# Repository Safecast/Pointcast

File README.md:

# Pointcast V1.0
New generation nGeigie (work in progress)

Uploads are done through the gateway and go to http://dev.safecast.org

simple software setup:
  - arduino ide 
  - teensyduino or teensy application for uploading hex file into Teensy
  - upgrade firmware instructions are at https://docs.google.com/document/d/16hdhQj_UQkusotejkor8-5BlaK_a2mFPmyVPtsAJ4F8/edit?usp=sharing

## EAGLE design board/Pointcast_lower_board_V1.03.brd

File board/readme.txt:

Files are cretaed in Eagle software

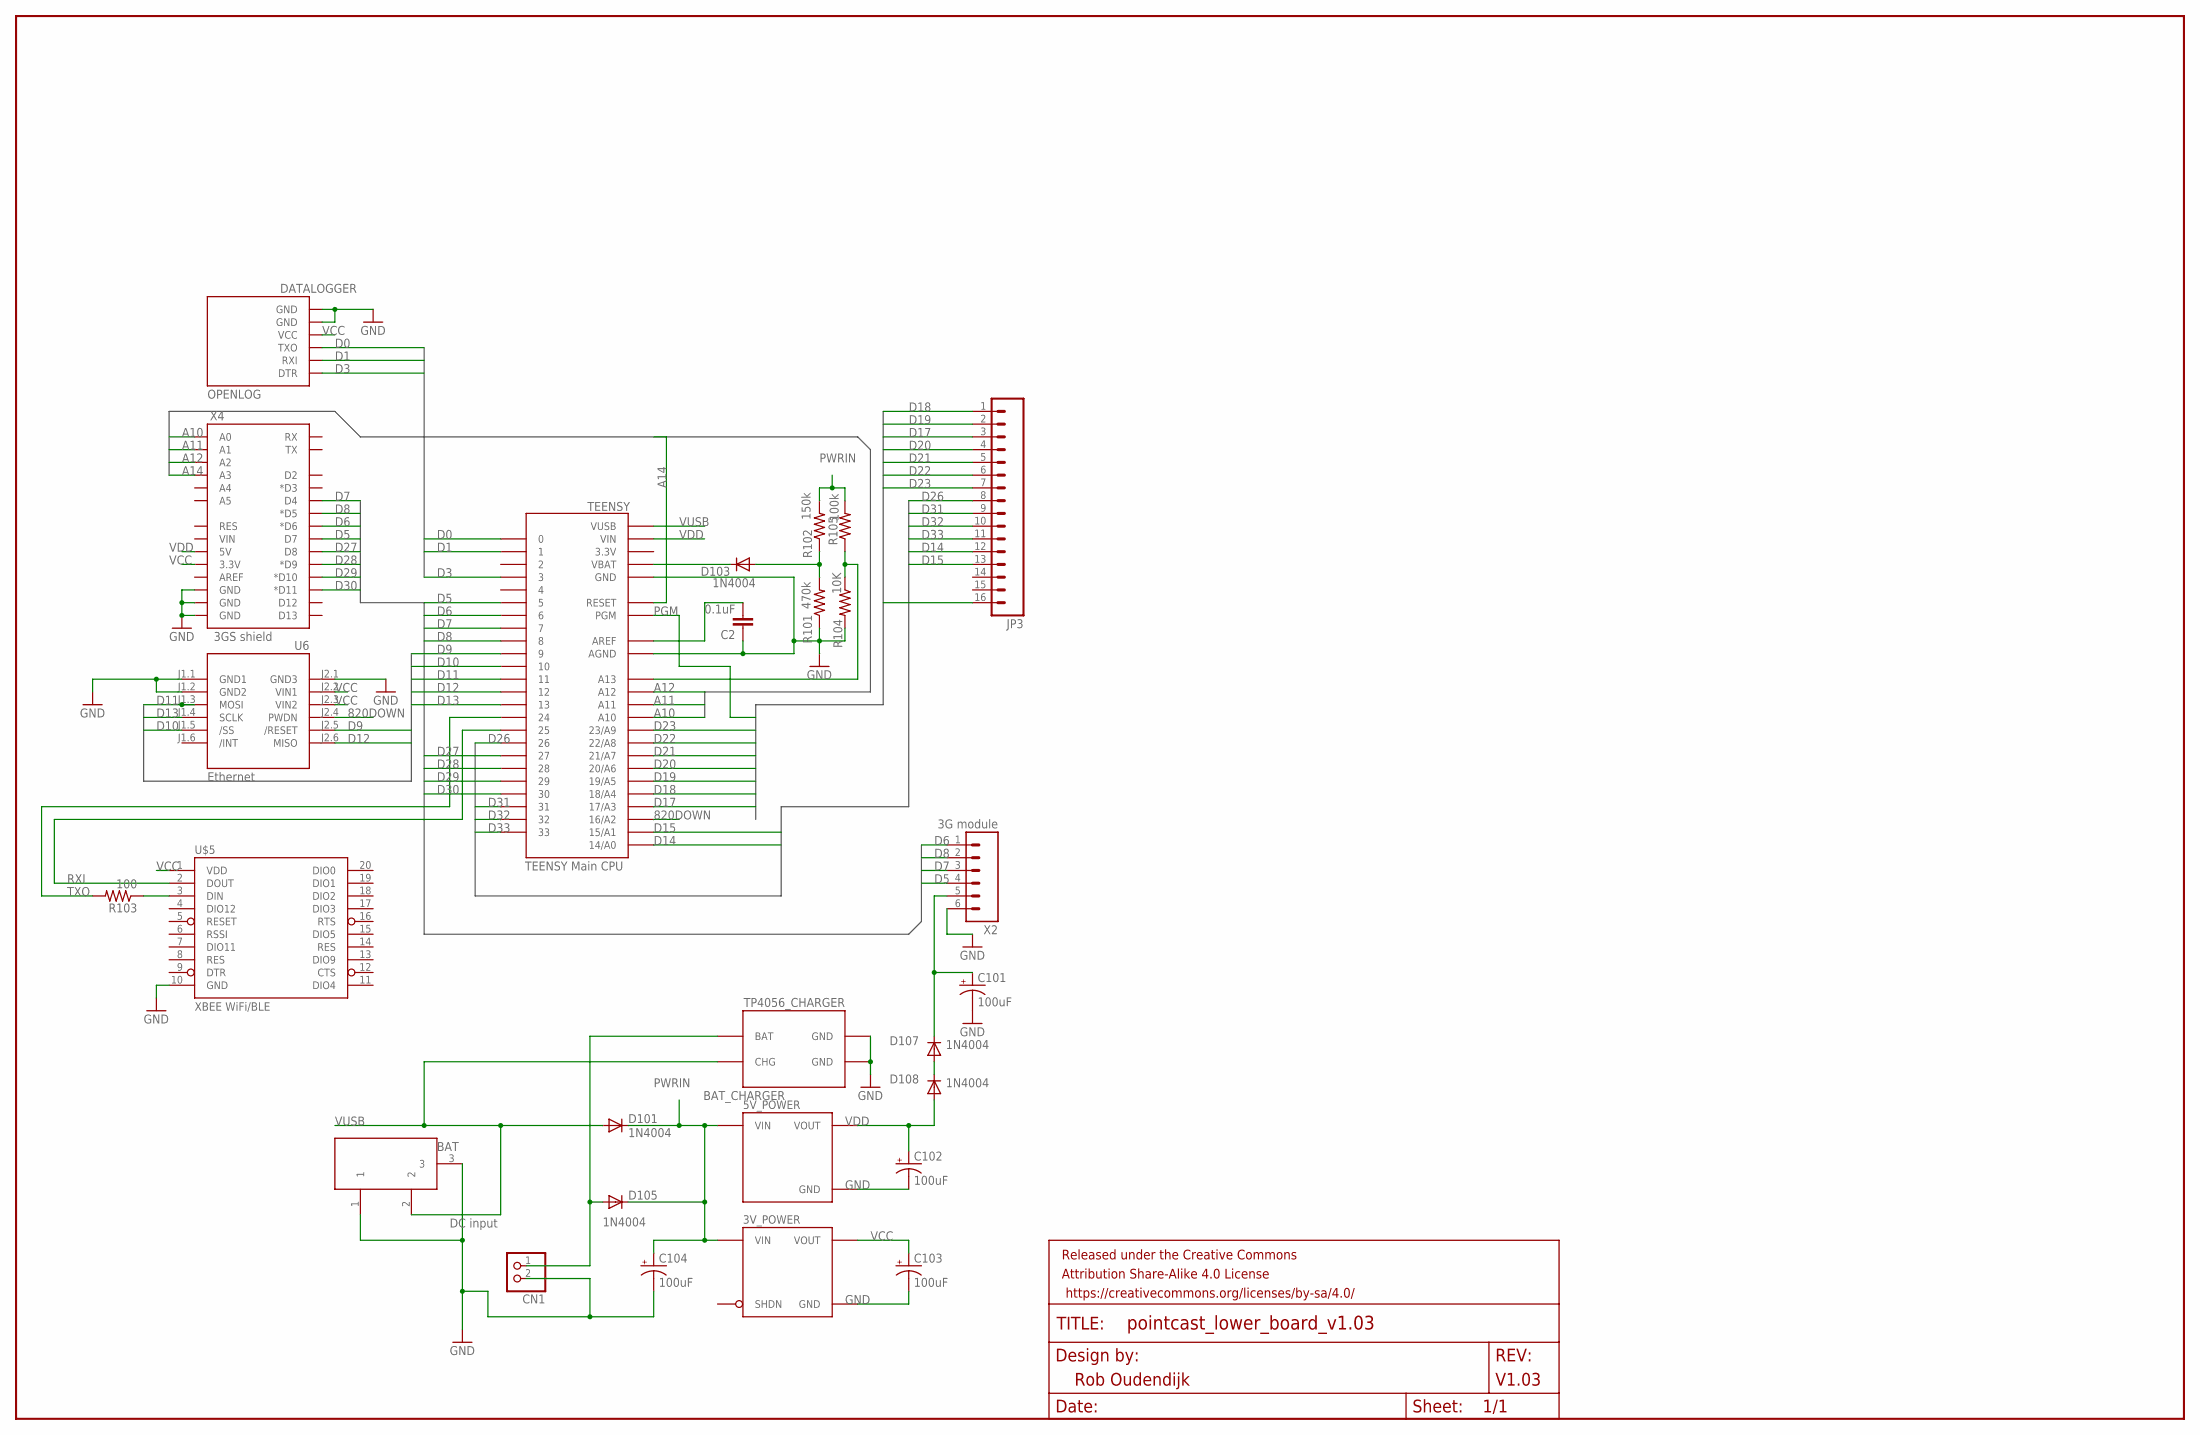
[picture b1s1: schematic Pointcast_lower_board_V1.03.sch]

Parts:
3V_POWER: POLOLU_D24V3AXV; POLOLU_D24VXAYV_HC
5V_POWER: POLOLU_S7V8F5
BAT_CHARGER: TP4056_CHARGER; TP4056
C2: 0.1uF; C025-024X044
C101, C102, C103, C104: 100uF; CPOL-RADIAL-100UF-25V
CN1: JST_2PIN-THM-RA; JST-PH-2-THM-RA
D101, D103, D105, D107, D108: 1N4004; DO41-10
DATALOGGER: OPENLOG
DCINPUT: 5Volt; DC-21MM
FRAME1: FRAME-LEDGER; CREATIVE_COMMONS
JP3: M16PTH; 1X16
R101: 470k; 0207/10
R102: 150k; 0207/10
R103: 100; 0207/10
R104: 10K; 0207/10
R105: 100k; 0207/10
TEENSY: TEENSY Main CPU; TEENSY_3.0_ALLPINS
U6: Ethernet; WIZ820IO
U$5: XBEE WiFi/BLE; XBEE-SILK
X2: 3G module; 1X06
X4: 3GS shield; DUEMILANOVE_SHIELD

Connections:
820DOWN: TEENSY.16/A2, U6.J2.4 (PWDN)
A10: TEENSY.A10, X4.A0
A11: TEENSY.A11, X4.A1
A12: TEENSY.A12, X4.A2
A14: TEENSY.RESET, X4.A3
BAT: BAT_CHARGER.BAT, CN1.1 (2), D105.A
D0: DATALOGGER.JP1$3 (TXO), TEENSY.0
D1: DATALOGGER.JP1$2 (RXI), TEENSY.1
D3: DATALOGGER.JP1$1 (DTR), TEENSY.3
D5: TEENSY.5, X2.4, X4.D7
D6: TEENSY.6, X2.1, X4.D6 (*D6)
D7: TEENSY.7, X2.3, X4.D4
D8: TEENSY.8, X2.2, X4.D5 (*D5)
D9: TEENSY.9, U6.J2.5 (/RESET)
D10: TEENSY.10, U6.J1.5 (/SS)
D11: TEENSY.11, U6.J1.3 (MOSI)
D12: TEENSY.12, U6.J2.6 (MISO)
D13: TEENSY.13, U6.J1.4 (SCLK)
D14: JP3.12, TEENSY.14/A0
D15: JP3.13, TEENSY.15/A1
D17: JP3.3, TEENSY.17/A3
D18: JP3.1, TEENSY.18/A4
D19: JP3.2, TEENSY.19/A5
D20: JP3.4, TEENSY.20/A6
D21: JP3.5, TEENSY.21/A7
D22: JP3.6, TEENSY.22/A8
D23: JP3.7, TEENSY.23/A9
D26: JP3.8, TEENSY.26
D27: TEENSY.27, X4.D8
D28: TEENSY.28, X4.D9 (*D9)
D29: TEENSY.29, X4.D10 (*D10)
D30: TEENSY.30, X4.D11 (*D11)
D31: JP3.9, TEENSY.31
D32: JP3.10, TEENSY.32
D33: JP3.11, TEENSY.33
GND: 3V_POWER.G (GND), 5V_POWER.G (GND), BAT_CHARGER.GND, BAT_CHARGER.GND2 (GND), C2.1, C101.1 (-), C102.1 (-), C103.1 (-), C104.1 (-), CN1.2 (1), DATALOGGER.JP1$5 (GND), DATALOGGER.JP1$6 (GND), DCINPUT.1, DCINPUT.3, R101.1, R104.2, TEENSY.AGND, TEENSY.GND, TEENSY.GND1 (GND), TEENSY.GND2 (GND), U6.J1.1 (GND1), U6.J1.2 (GND2), U6.J2.1 (GND3), U$5.10 (GND), X2.6, X4.GND@0 (GND), X4.GND@1 (GND), X4.GND@2 (GND)
unnamed: D103.C, TEENSY.VBAT
unnamed: D103.A, R101.2, R102.1
unnamed: R104.1, R105.1, TEENSY.A13
unnamed: R103.1, U$5.3 (DIN)
unnamed: C2.2, TEENSY.AREF
unnamed: D107.A, D108.C
unnamed: C101.2 (+), D107.C, X2.5
PGM: JP3.16, TEENSY.PGM
PWRIN: 3V_POWER.I (VIN), 5V_POWER.I (VIN), C104.2 (+), D101.C, D105.C, R102.2, R105.2
RXI: TEENSY.25, U$5.2 (DOUT)
TXO: R103.2, TEENSY.24
VCC: 3V_POWER.O (VOUT), C103.2 (+), DATALOGGER.JP1$4 (VCC), U6.J2.2 (VIN1), U6.J2.3 (VIN2), U$5.1 (VDD), X4.3.3V
VDD: 5V_POWER.O (VOUT), C102.2 (+), D108.A, TEENSY.VIN, X4.5V
VUSB: BAT_CHARGER.CHARGER (CHG), D101.A, DCINPUT.2, TEENSY.VUSB

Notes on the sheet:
DC input

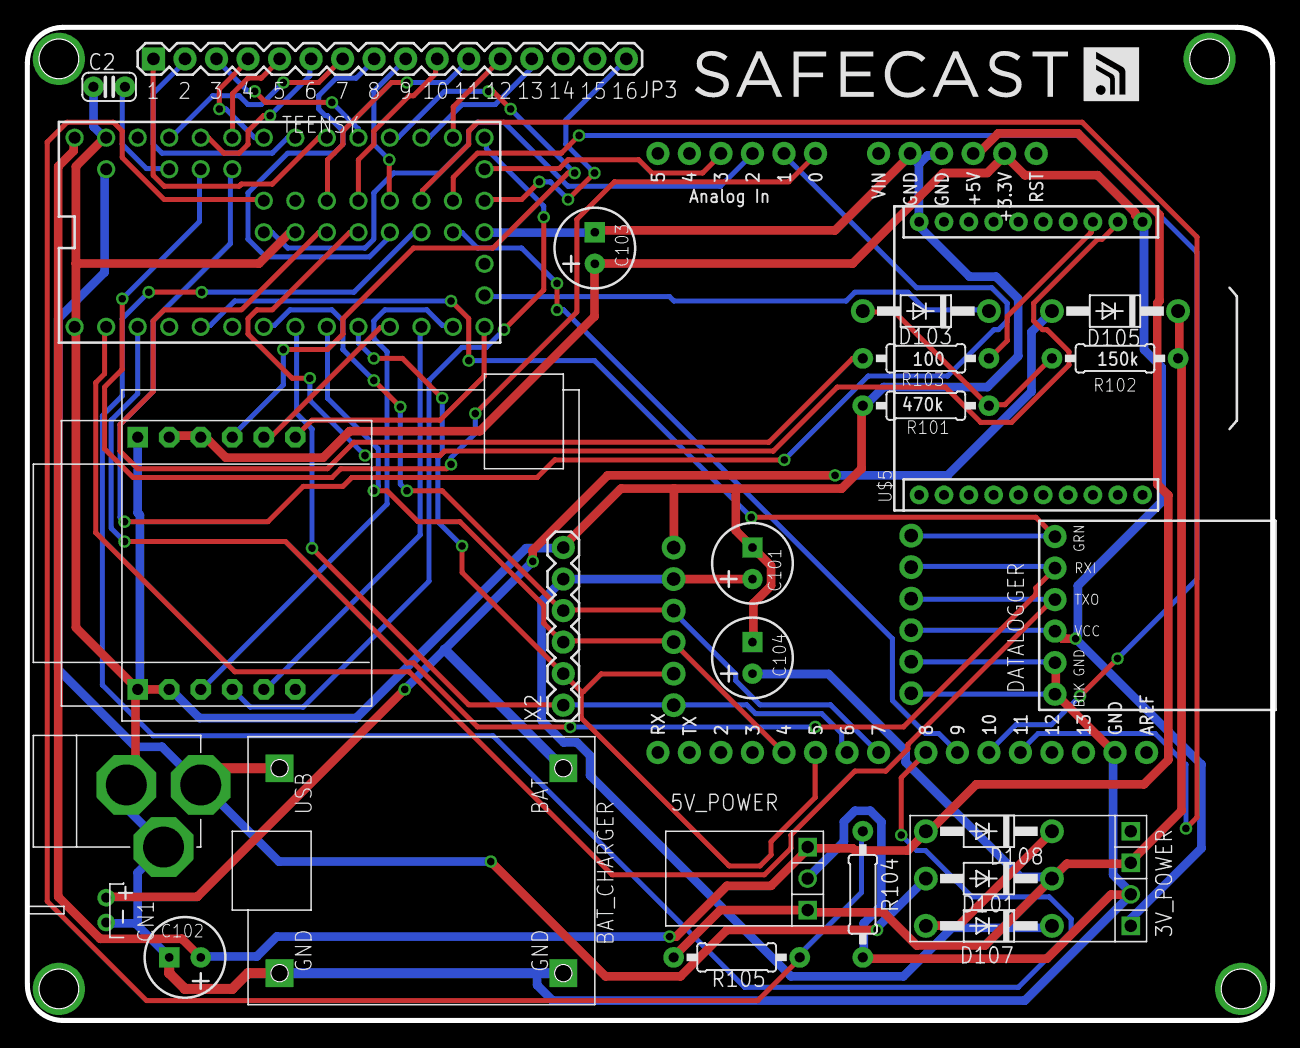
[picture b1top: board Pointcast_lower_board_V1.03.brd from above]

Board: 2 copper layers, 100.3 x 80.0 mm, 29 parts (0 on the bottom side), 50 nets.

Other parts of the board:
U$10: SAFECAST_LOGO1

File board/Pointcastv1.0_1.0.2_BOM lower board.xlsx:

Part | Value | Device | Package | Description | PROD_ID
3V_POWER |  | POLOLU_D24V3AXV | POLOLU_D24VXAYV_HC | Pololu Adjustable Step Down Voltage Regulators Series D24V3A_V (300 mA)0.4x0.6""
5V_POWER |  | POLOLU_S7V8F5 | POLOLU_S7V8F5 | POLOLU_S7V8F5
BAT_CHARGER | TP4056_CHARGER | TP4056_CHARGER | TP4056 | TP4056
C2 | 0.1uF | C-EU025-024X044 | C025-024X044 | CAPACITOR, European symbol
C101 | 100uF | CAP_POLPTH1 | CPOL-RADIAL-100UF-25V | Capacitor Polarized
C102 | 100uF | CAP_POLPTH1 | CPOL-RADIAL-100UF-25V | Capacitor Polarized
C103 | 100uF | CAP_POLPTH1 | CPOL-RADIAL-100UF-25V | Capacitor Polarized
C104 | 100uF | CAP_POLPTH1 | CPOL-RADIAL-100UF-25V | Capacitor Polarized
CN1 |  | JST_2PIN-THM-RA | JST-PH-2-THM-RA | JST 2-Pin Connectors of various flavors
D101 | 1N4004 | 1N4004 | DO41-10 | DIODE
D103 | 1N4004 | 1N4004 | DO41-10 | DIODE
D105 | 1N4004 | 1N4004 | DO41-10 | DIODE
D107 | 1N4004 | 1N4004 | DO41-10 | DIODE
D108 | 1N4004 | 1N4004 | DO41-10 | DIODE
DATALOGGER | OPENLOG | OPENLOG | OPENLOG | Openlog
DCINPUT | 5Volt | DC21MMX | DC-21MM
FRAME1 | FRAME-LEDGER | FRAME-LEDGER | CREATIVE_COMMONS | Schematic Frame
JP3 |  | M16PTH | 1X16 | 1x16 .1 header"
R101 | 470k | R-US_0207/10 | 0207/10 | RESISTOR, American symbol
R102 | 150k | R-US_0207/10 | 0207/10 | RESISTOR, American symbol
R103 | 100 | R-US_0207/10 | 0207/10 | RESISTOR, American symbol
R104 | 10K | R-US_0207/10 | 0207/10 | RESISTOR, American symbol
R105 | 100k | R-US_0207/10 | 0207/10 | RESISTOR, American symbol
TEENSY | TEENSY Main CPU | TEENSY_3.0_ALLPINS | TEENSY_3.0_ALLPINS | Teensy 3.0 with all pin holes and optional SMD-mount unshrouded header on botto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
U$5 | XBEE WiFi/BLE | XBEE-2B2 | XBEE-SILK | Xbee module footprints
U6 | Ethernet | WIZ820IO_DEVICE'DUAL-IN-LINE' | WIZ820IO | WIZnet, WIZ820io plug in module incl. W5200 chip and MagJack
X2 | 3G module | M06SILK_FEMALE_PTH | 1X06 | Header 6 | CONN-08437
X4 | 3GS shield | ARDUINO_SHIELDLABEL | DUEMILANOVE_SHIELD | Arduino shield footprint

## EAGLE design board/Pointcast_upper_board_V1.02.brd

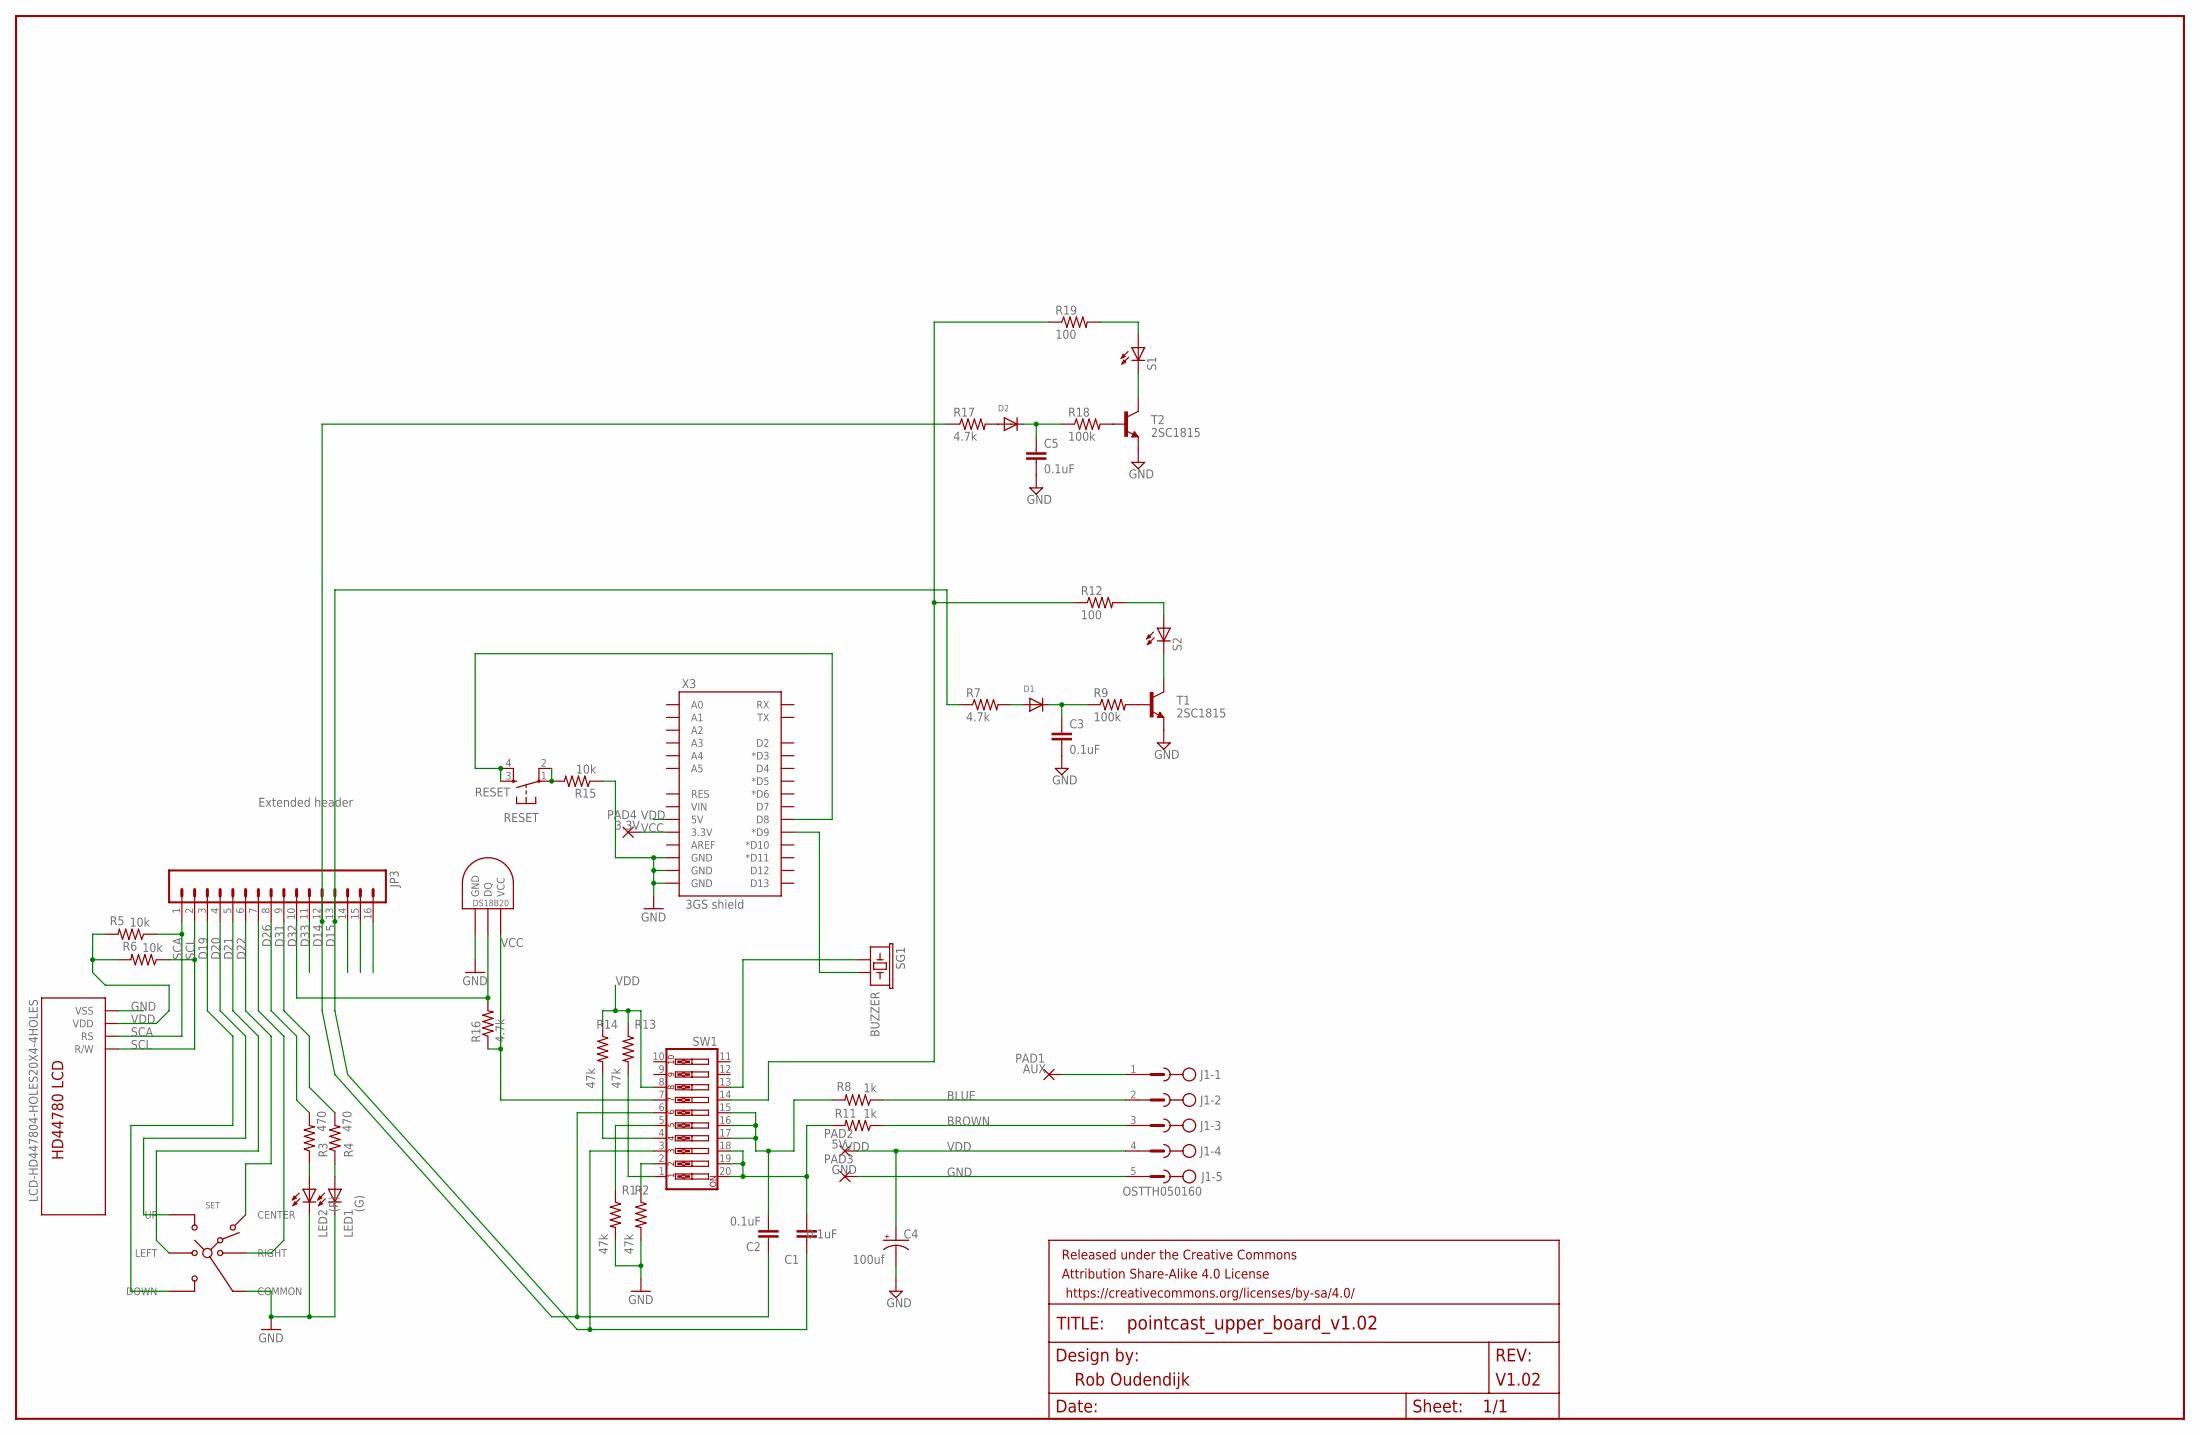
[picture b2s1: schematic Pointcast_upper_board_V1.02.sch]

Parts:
C1, C2, C3, C5: 0.1uF; C025-024X044
C4: 100uf; CPOL-RADIAL-100UF-25V
D1, D2: DIODEDIODE_BIG; DO41-10
FRAME1: FRAME-LEDGER; CREATIVE_COMMONS
J1: OSTTH050160; EDSTL130-05
JP3: Extended header; 1X16
LED1: (G); LED3MM
LED2: (R); LED3MM
PAD1: AUX; 2,15/1,0
PAD2: 5V; 2,15/1,0
PAD3: GND; 2,15/1,0
PAD4: 3.3V; 2,15/1,0
R1, R2, R13, R14: 47k; 0207/10
R3, R4: 470; 0207/10
R5, R6, R15: 10k; 0207/10
R7, R16, R17: 4.7k; 0207/10
R8, R11: 1k; 0207/10
R9, R18: 100k; 0207/10
R12, R19: 100; 0207/10
RESET: RESET; DTS-6
S1, S2: LED3MM
SET: SKQUCAA010; SKQU
SG1: BUZZER; BUZZER-12MM
SW1: SW_DIP-10; EDG-10
T1, T2: 2SC1815; TO92-ECB
TEMP: AVA_DS1820TO92; AVA_DS1820
X1: LCD-HD447804-HOLES20X4-4HOLES; LCD-20X4-4HOLES
X3: 3GS shield; DUEMILANOVE_SHIELD

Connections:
BLUE: J1.2, R8.1
BROWN: J1.3, R11.1
D14: C2.1, JP3.12, R17.1, SW1.6
D15: C1.1, JP3.13, R7.1, SW1.3
D19: JP3.3, SET.DOWN
D20: JP3.4, SET.UP
D21: JP3.5, SET.LEFT
D22: JP3.6, SET.CENTER
D26: JP3.8, R3.2
D31: JP3.9, R4.2
D32: JP3.10, R16.2, TEMP.DQ
D33: JP3.11
GND: C3.2, C4.1 (-), C5.2, J1.5, LED1.K (C), LED2.K (C), PAD3.1, R1.2, R2.2, R15.1, SET.COMMON, T1.E, T2.E, TEMP.GND, X1.P$13 (VSS), X3.GND@0 (GND), X3.GND@1 (GND), X3.GND@2 (GND)
unnamed: SG1.+ (1), SW1.13
unnamed: LED2.A, R3.1
unnamed: R14.2, SW1.4
unnamed: R12.1, R19.1, SW1.14
unnamed: R2.1, SW1.2
unnamed: R1.1, SW1.5
unnamed: J1.1, PAD1.1
unnamed: SG1.- (2), X3.D9 (*D9)
unnamed: C1.2, R11.2, SW1.18, SW1.19, SW1.20
unnamed: R13.2, SW1.1
unnamed: D1.A, R7.2
unnamed: C3.1, D1.C, R9.1
unnamed: LED1.A, R4.1
unnamed: R9.2, T1.B
unnamed: S2.K (C), T1.C
unnamed: R15.2, RESET.1, RESET.2
unnamed: RESET.3, RESET.4, X3.D8
unnamed: R12.2, S2.A
unnamed: D2.A, R17.2
unnamed: C5.1, D2.C, R18.1
unnamed: R18.2, T2.B
unnamed: S1.K (C), T2.C
unnamed: R19.2, S1.A
unnamed: C2.2, R8.2, SW1.15, SW1.16, SW1.17
S$5: JP3.7, SET.RIGHT
SCA: JP3.1, R5.1, X1.P$15 (RS)
SCL: JP3.2, R6.1, X1.P$16 (R/W)
VCC: PAD4.1, R16.1, SW1.7, TEMP.VDD (VCC), X3.3.3V
VDD: C4.2 (+), J1.4, PAD2.1, R5.2, R6.2, R13.1, R14.1, SW1.8, X1.P$14 (VDD), X3.5V

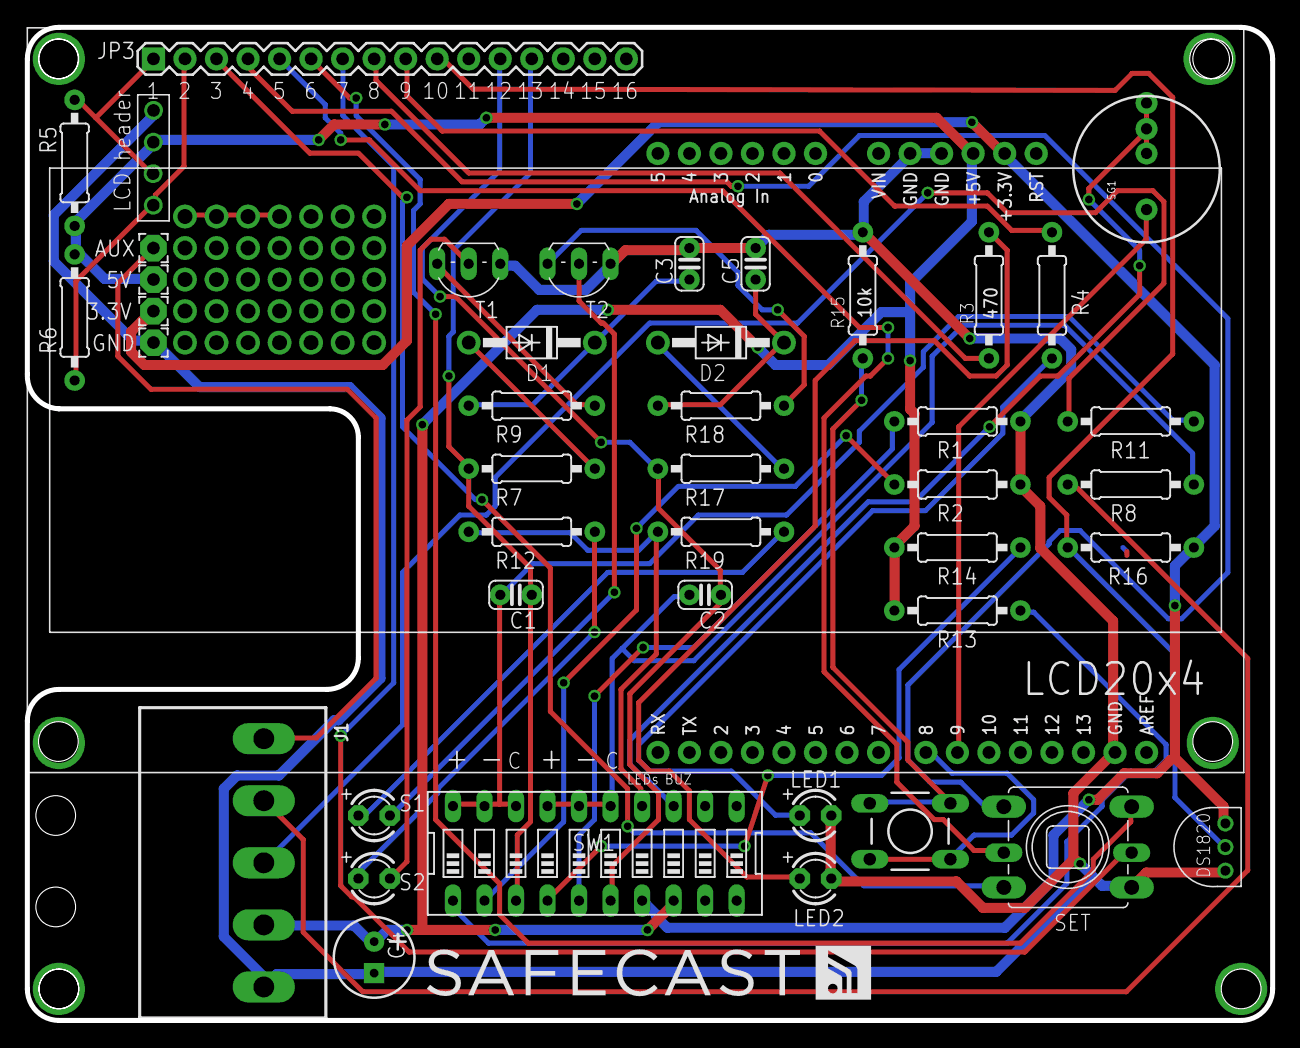
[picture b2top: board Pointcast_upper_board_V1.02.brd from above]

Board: 2 copper layers, 100.3 x 80.0 mm, 46 parts (0 on the bottom side), 41 nets.

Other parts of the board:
U$10: SAFECAST_LOGO1

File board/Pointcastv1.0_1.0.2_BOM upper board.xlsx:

Part | Value | Device | Package | Description | MF | OC_ADAFRUIT | OC_MOUSER | OC_NEWARK
C1 | 0.1uF | C-EU025-024X044 | C025-024X044 | CAPACITOR, European symbol
C2 | 0.1uF | C-EU025-024X044 | C025-024X044 | CAPACITOR, European symbol
C3 | 0.1uF | C-EU025-024X044 | C025-024X044 | CAPACITOR, European symbol
C4 | 100uf | CAP_POLPTH1 | CPOL-RADIAL-100UF-25V | Capacitor Polarized
C5 | 0.1uF | C-EU025-024X044 | C025-024X044 | CAPACITOR, European symbol
D1 |  | DIODEDIODE_BIG | DO41-10 | Diode
D2 |  | DIODEDIODE_BIG | DO41-10 | Diode
FRAME1 | FRAME-LEDGER | FRAME-LEDGER | CREATIVE_COMMONS | Schematic Frame
J1 | OSTTH050160 | OSTTH050160 | EDSTL130-05 | 5mm Terminal Header
JP3 | Extended header | M16PTH | 1X16 | 1x16 .1 header"
LED1 | (G) | LED3MM | LED3MM | LED
LED2 | (R) | LED3MM | LED3MM | LED
PAD1 | AUX | 2,15/1,0 | 2,15/1,0 | THROUGH-HOLE PAD
PAD2 | 5V | 2,15/1,0 | 2,15/1,0 | THROUGH-HOLE PAD
PAD3 | GND | 2,15/1,0 | 2,15/1,0 | THROUGH-HOLE PAD
PAD4 | 3.3V | 2,15/1,0 | 2,15/1,0 | THROUGH-HOLE PAD
R1 | 47k | R-US_0207/10 | 0207/10 | RESISTOR, American symbol
R2 | 47k | R-US_0207/10 | 0207/10 | RESISTOR, American symbol
R3 | 470 | R-US_0207/10 | 0207/10 | RESISTOR, American symbol
R4 | 470 | R-US_0207/10 | 0207/10 | RESISTOR, American symbol
R5 | 10k | R-US_0207/10 | 0207/10 | RESISTOR, American symbol
R6 | 10k | R-US_0207/10 | 0207/10 | RESISTOR, American symbol
R7 | 4.7k | R-US_0207/10 | 0207/10 | RESISTOR, American symbol
R8 | 1k | R-US_0207/10 | 0207/10 | RESISTOR, American symbol
R9 | 100k | R-US_0207/10 | 0207/10 | RESISTOR, American symbol
R11 | 1k | R-US_0207/10 | 0207/10 | RESISTOR, American symbol
R12 | 100 | R-US_0207/10 | 0207/10 | RESISTOR, American symbol
R13 | 47k | R-US_0207/10 | 0207/10 | RESISTOR, American symbol
R14 | 47k | R-US_0207/10 | 0207/10 | RESISTOR, American symbol
R15 | 10k | R-US_0207/10 | 0207/10 | RESISTOR, American symbol
R16 | 4.7k | R-US_0207/10 | 0207/10 | RESISTOR, American symbol
R17 | 4.7k | R-US_0207/10 | 0207/10 | RESISTOR, American symbol
R18 | 100k | R-US_0207/10 | 0207/10 | RESISTOR, American symbol
R19 | 100 | R-US_0207/10 | 0207/10 | RESISTOR, American symbol
RESET | RESET | DTS-6 | DTS-6
S1 |  | LED3MM | LED3MM | LED
S2 |  | LED3MM | LED3MM | LED
SET |  | SKQUCAA010 | SKQU | Multi Control Devices TACT Switch - 4-directional with Center Push Type. | ALPS | 504 | 688-SKQUCA | 59M1983
SG1 | BUZZER | BUZZERPTH | BUZZER-12MM | Buzzer 12mm
SW1 |  | SW_DIP-10 | EDG-10 | DIP SWITCH
T1 | 2SC1815 | 2SC1815 | TO92-ECB | NPN EPITAXIAL TRANSISTOR
T2 | 2SC1815 | 2SC1815 | TO92-ECB | NPN EPITAXIAL TRANSISTOR
TEMP | AVA_DS1820TO92 | AVA_DS1820TO92 | AVA_DS1820 | DS18B20
X1 | LCD-HD447804-HOLES20X4-4HOLES | LCD-HD447804-HOLES20X4-4HOLES | LCD-20X4-4HOLES
X3 | 3GS shield | ARDUINO_SHIELDLABEL | DUEMILANOVE_SHIELD | Arduino shield footprint

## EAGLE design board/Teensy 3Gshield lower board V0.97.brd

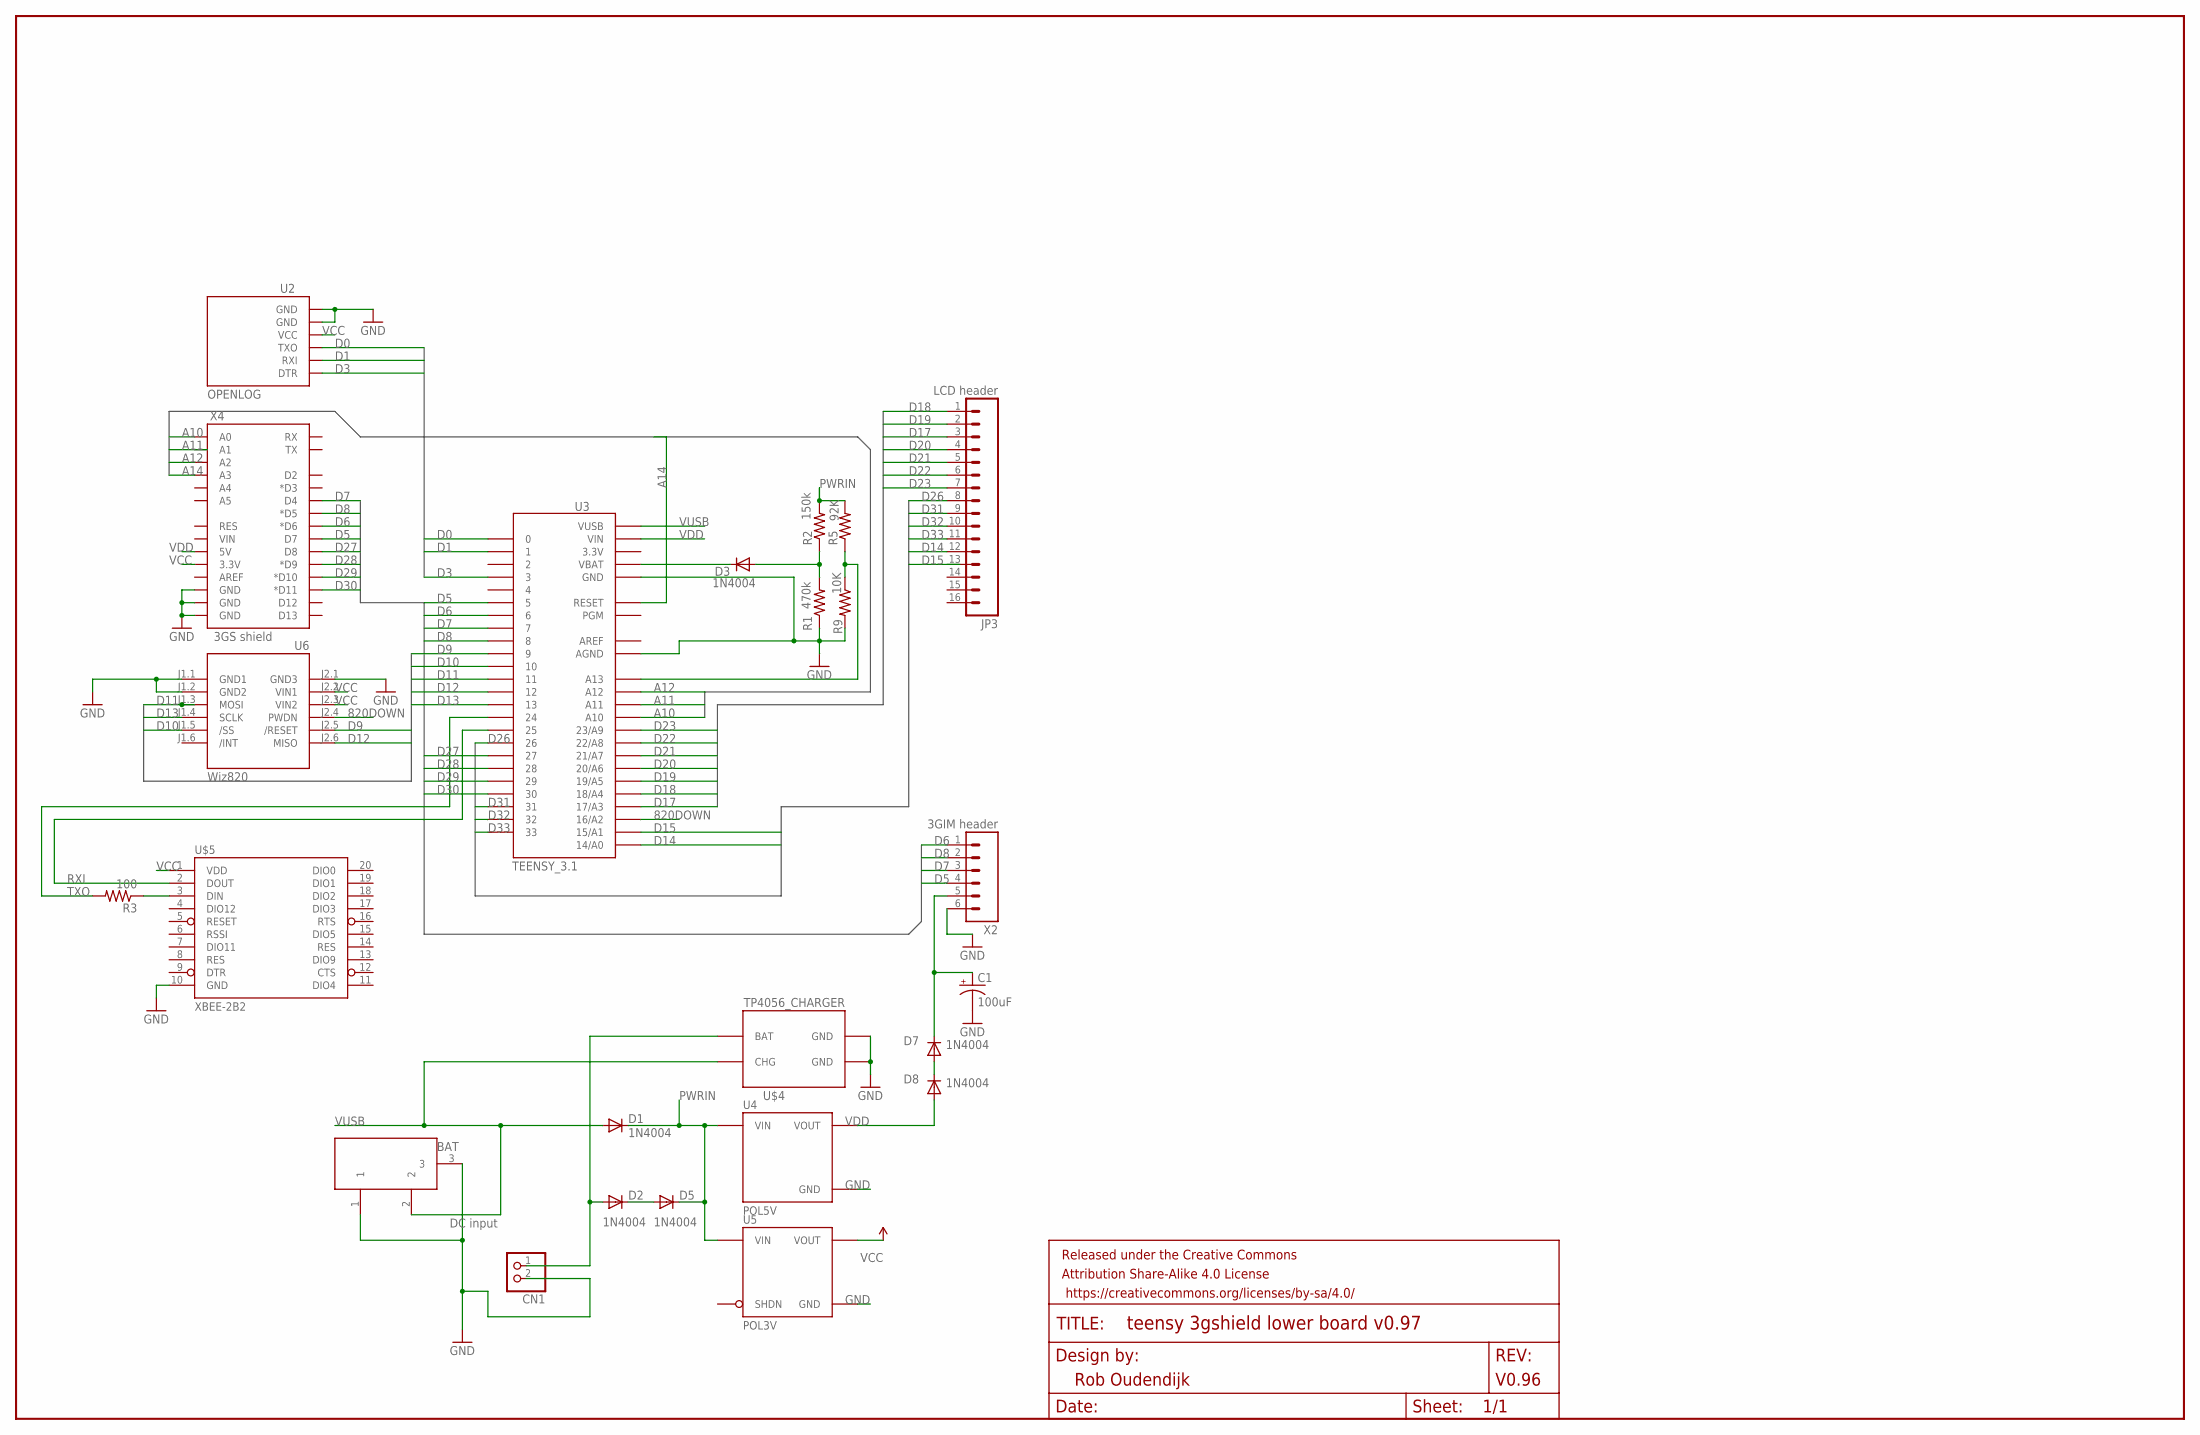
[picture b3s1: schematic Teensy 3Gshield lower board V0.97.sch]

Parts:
C1: 100uF; CPOL-RADIAL-100UF-25V
CN1: JST_2PIN-THM-RA; JST-PH-2-THM-RA
D1, D2, D3, D5, D7, D8: 1N4004; DO41-10
DCINPUT: DC21MMX; DC-21MM
FRAME1: FRAME-LEDGER; CREATIVE_COMMONS
JP3: LCD header; 1X16
R1: 470k; AXIAL-0.3EZ
R2: 150k; AXIAL-0.3EZ
R3: 100; AXIAL-0.3EZ
R5: 92K; AXIAL-0.3EZ
R9: 10K; AXIAL-0.3EZ
U2: OPENLOG
U3: TEENSY_3.1; TEENSY_3.0_ALLPINS
U4: POL5V; POLOLU_S7V8F5
U5: POL3V; POLOLU_D24VXAYV_HC
U6: Wiz820; WIZ820IO
U$4: TP4056_CHARGER; TP4056
U$5: XBEE-2B2; XBEE-SILK
X2: 3GIM header; 1X06
X4: 3GS shield; DUEMILANOVE_SHIELD

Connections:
820DOWN: U3.16/A2, U6.J2.4 (PWDN)
A10: U3.A10, X4.A0
A11: U3.A11, X4.A1
A12: X4.A2
A14: U3.RESET, X4.A3
AREF: U3.AREF
BAT: CN1.1 (2), D2.A, U$4.BAT
D0: U2.JP1$3 (TXO), U3.0
D1: U2.JP1$2 (RXI), U3.1
D3: U2.JP1$1 (DTR), U3.3
D5: U3.5, X2.4, X4.D7
D6: U3.6, X2.1, X4.D6 (*D6)
D7: U3.7, X2.3, X4.D4
D8: U3.8, X2.2, X4.D5 (*D5)
D9: U3.9, U6.J2.5 (/RESET)
D10: U3.10, U6.J1.5 (/SS)
D11: U3.11, U6.J1.3 (MOSI)
D12: U3.12, U6.J2.6 (MISO)
D13: U3.13, U6.J1.4 (SCLK)
D14: JP3.12, U3.14/A0
D15: U3.15/A1
D17: JP3.3, U3.17/A3
D18: JP3.1, U3.18/A4
D19: JP3.2, U3.19/A5
D20: JP3.4, U3.20/A6
D21: JP3.5, U3.21/A7
D22: JP3.6, U3.22/A8
D23: JP3.7, U3.23/A9
D26: JP3.8, U3.26
D27: U3.27, X4.D8
D28: U3.28, X4.D9 (*D9)
D29: U3.29, X4.D10 (*D10)
D30: U3.30, X4.D11 (*D11)
D31: JP3.9, U3.31
D32: JP3.10, U3.32
D33: JP3.11, U3.33
GND: C1.2 (-), CN1.2 (1), DCINPUT.1, DCINPUT.3, R1.P$1 (1), R9.P$2 (2), U2.JP1$5 (GND), U2.JP1$6 (GND), U3.AGND, U3.GND, U3.GND1 (GND), U3.GND2 (GND), U4.G (GND), U5.G (GND), U6.J1.1 (GND1), U6.J1.2 (GND2), U6.J2.1 (GND3), U$4.GND, U$4.GND2 (GND), U$5.10 (GND), X2.6, X4.GND@0 (GND), X4.GND@1 (GND), X4.GND@2 (GND)
unnamed: D3.C, U3.VBAT
unnamed: D3.A, R1.P$2 (2), R2.P$1 (1)
unnamed: D2.C, D5.A
unnamed: R5.P$1 (1), R9.P$1 (1), U3.A13
unnamed: R3.P$1 (1), U$5.3 (DIN)
unnamed: D7.A, D8.C
unnamed: C1.1 (+), D7.C, X2.5
PWRIN: D1.C, D5.C, R2.P$2 (2), R5.P$2 (2), U4.I (VIN), U5.I (VIN)
RXI: U3.25, U$5.2 (DOUT)
TXO: R3.P$2 (2), U3.24
VCC: U2.JP1$4 (VCC), U5.O (VOUT), U6.J2.2 (VIN1), U6.J2.3 (VIN2), U$5.1 (VDD), X4.3.3V
VDD: D8.A, U3.VIN, U4.O (VOUT), X4.5V
VUSB: D1.A, DCINPUT.2, U3.VUSB, U$4.CHARGER (CHG)

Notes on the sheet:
DC input

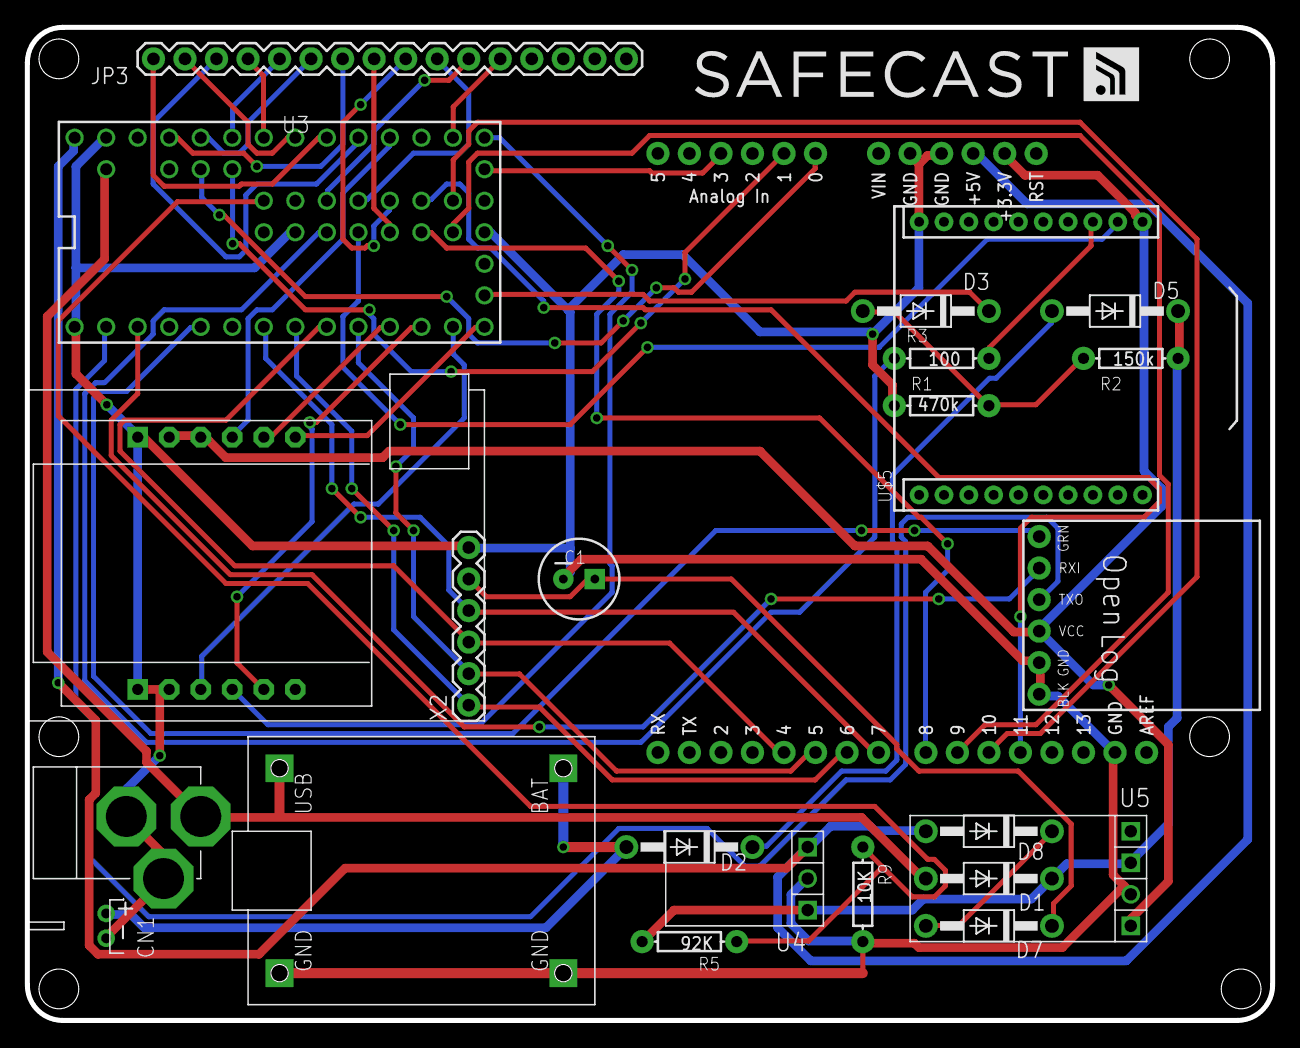
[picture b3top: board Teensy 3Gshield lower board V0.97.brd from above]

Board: 2 copper layers, 100.3 x 80.0 mm, 26 parts (0 on the bottom side), 47 nets.

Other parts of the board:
U$10: SAFECAST_LOGO1

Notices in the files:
parts and their libraries:
SparkFun-Connectors: Licensing: Creative Commons ShareAlike 4.0 International - https://creativecommons.org/licenses/by-sa/4.0
SparkFun-Aesthetics: Released under the Creative Commons
SparkFun-Aesthetics: https://creativecommons.org/licenses/by-sa/4.0
con-ost: Copyright (C) 2008, Bob Starr
